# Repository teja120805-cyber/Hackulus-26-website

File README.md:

# ESP32-C3 Nano

:warning: **Temporary warning**: This version of PCB has not been yet validated and it is actively being worked on

Compact and minimalist **ESP32-C3** breakout designed in [KiCAD](https://www.kicad.org/)

## Features
- **Breadboard friendly**
- **Compact dimensions** - 46 x 21.5 mm
- **USB-C** connector for programming (using CDC, so no external usb-serial convertor)
- **External VIN pin** with schottky diode (so both VIN and USB power can be applied at the same time)
- **Low dropout regulator to 3V3** (LDO)
- **Reset** and **Boot** buttons on board
- **Integrated PCB antenna**
- **USB ESD protection**
- Chip: **ESP32-C3FH4**

## Interactive HTML BOM
Thanks to the awesome KiCAD [IBOM](https://github.com/openscopeproject/InteractiveHtmlBom) plugin, we can now generate this stunning BOM! You can find it in docs/ibom.html

## Schematics

## Contributors:
- **SZKANDERA Filip** (filip.szkandera@gmail.com, [@FilipSzkandera](https://github.com/FilipSzkandera/))
- **FRYČÁK Tadeáš** (info@frycak.com, [@TadeasFrycak](https://github.com/TadeasFrycak/))

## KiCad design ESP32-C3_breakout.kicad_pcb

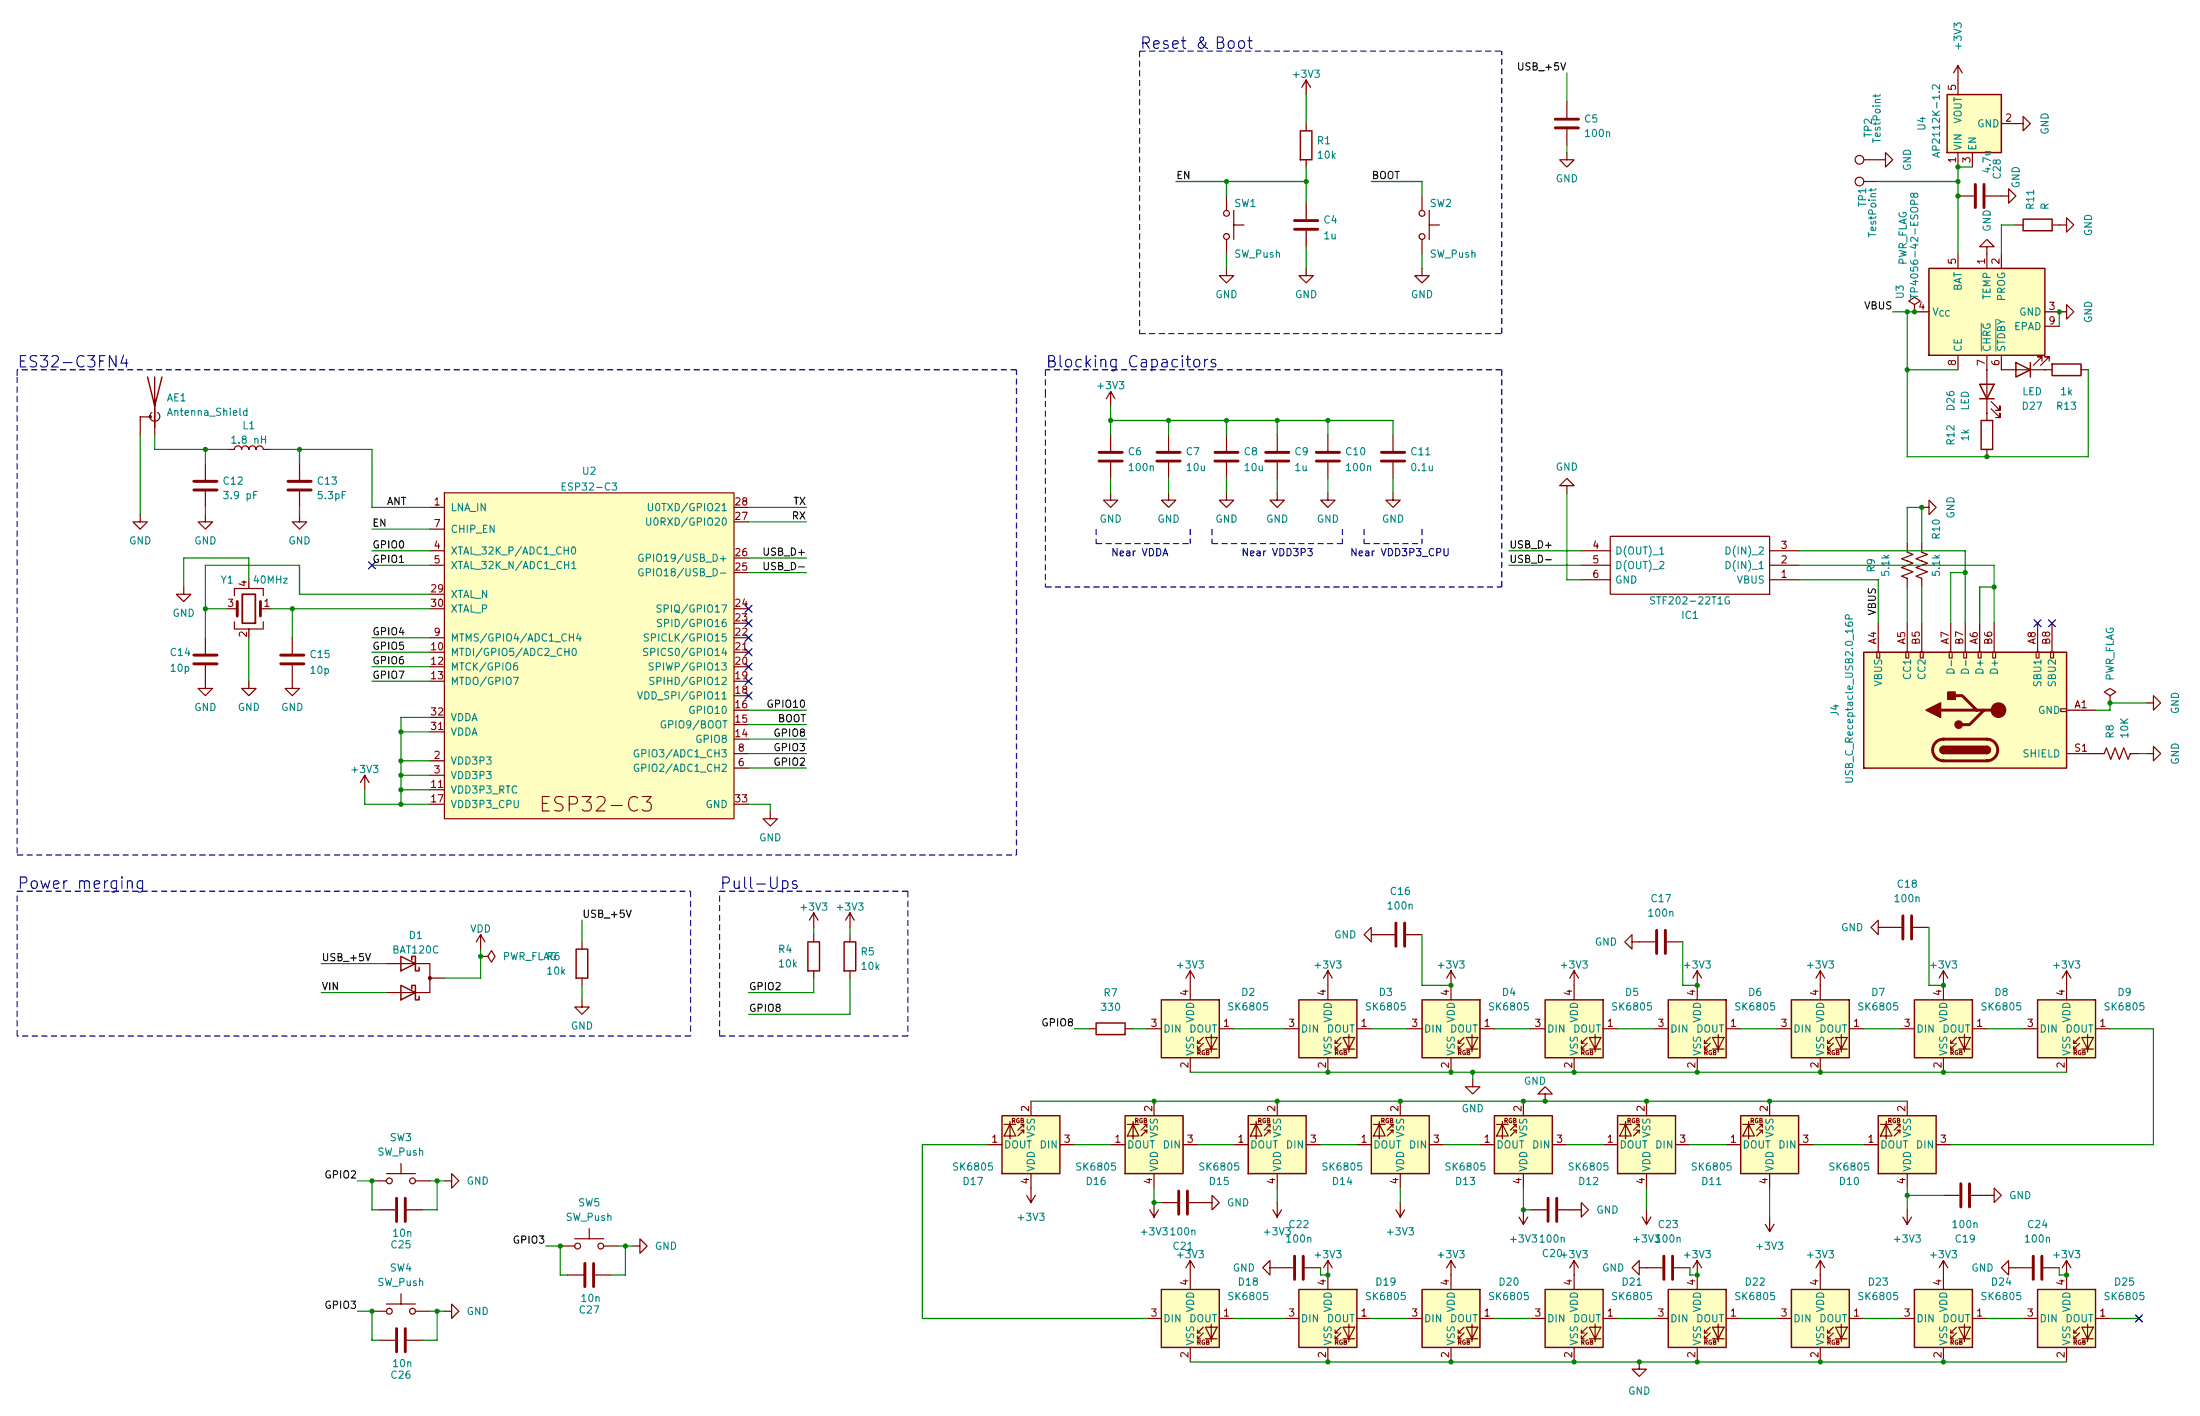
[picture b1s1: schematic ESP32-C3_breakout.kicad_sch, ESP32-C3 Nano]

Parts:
AE1: Antenna_Shield; ESPRESSIF_ESP32_MIFA_2.4GHz_Right
C4, C9: 1u; C_0603_1608Metric
C5, C6, C10, C16, C17, C18, C19, C20, C21, C22, C23, C24: 100n; C_0603_1608Metric
C7, C8: 10u; C_0603_1608Metric
C11: 0.1u; C_0603_1608Metric
C12: 3.9 pF; C_0603_1608Metric
C13: 5.3pF; C_0603_1608Metric
C14, C15: 10p; C_0603_1608Metric
C25, C26, C27: 10n; C_0603_1608Metric
C28: 4.7u; C_0603_1608Metric
D1: BAT120C; SOT-223
D2, D3, D4, D5, D6, D7, D8, D9, D10, D11, D12, D13, D14, D15, D16, D17, D18, D19, D20, D21, D22, D23, D24, D25: SK6805; LED_SK6805_PLCC4_2.4x2.7mm_P1.3mm
D26, D27: LED; LED_0603_1608Metric
IC1: STF202-22T1G; TSOP-6_1.65x3.05mm_P0.95mm; Manufacturer_Part_Number STF202-22T1G; Mouser Part Number 863-STF202-22T1G
J4: USB_C_Receptacle_USB2.0_16P; USB_C_Receptacle_HRO_TYPE-C-31-M-12
L1: 1.8 nH; L_0603_1608Metric
R1, R4, R5, R6: 10k; R_0603_1608Metric
R7: 330; LED_SK6805_PLCC4_2.4x2.7mm_P1.3mm
R8: 10K; R_0603_1608Metric_Pad0.98x0.95mm_HandSolder
R9, R10: 5.1k; R_0603_1608Metric_Pad0.98x0.95mm_HandSolder
R11: R; LED_SK6805_PLCC4_2.4x2.7mm_P1.3mm
R12, R13: 1k; LED_SK6805_PLCC4_2.4x2.7mm_P1.3mm
SW1, SW2: SW_Push; SW_SPST_PTS810
SW3, SW4, SW5: SW_Push; Texas_RVA_VQFN-16-1EP_3.5x3.5mm_P0.5mm_EP2.14x2.14mm_Therma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
TP1, TP2: TestPoint; TestPoint_Pad_1.0x1.0mm
U2: ESP32-C3; QFN-32-1EP_5x5mm_P0.5mm_EP3.45x3.45mm
U3: TP4056-42-ESOP8; SOIC-8-1EP_3.9x4.9mm_P1.27mm_EP2.41x3.3mm_ThermalVias
U4: AP2112K-1.2; SOT-23-5
Y1: 40MHz; Crystal_SMD_2016-4Pin_2.0x1.6mm

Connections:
+3V3: C6.1, C7.1, C8.1, C9.1, C10.1, C11.1, C16.2, C17.2, C18.2, C19.2, C20.2, C21.2, C22.2, C23.2, C24.2, D2.4 (VDD), D3.4 (VDD), D4.4 (VDD), D5.4 (VDD), D6.4 (VDD), D7.4 (VDD), D8.4 (VDD), D9.4 (VDD), D10.4 (VDD), D11.4 (VDD), D12.4 (VDD), D13.4 (VDD), D14.4 (VDD), D15.4 (VDD), D16.4 (VDD), D17.4 (VDD), D18.4 (VDD), D19.4 (VDD), D20.4 (VDD), D21.4 (VDD), D22.4 (VDD), D23.4 (VDD), D24.4 (VDD), D25.4 (VDD), R1.1, R4.1, R5.1, U2.2 (VDD3P3), U2.3 (VDD3P3), U2.11 (VDD3P3_RTC), U2.17 (VDD3P3_CPU), U2.31 (VDDA), U2.32 (VDDA), U4.5 (VOUT)
/ANT: C13.1, L1.1, U2.1 (LNA_IN)
/BOOT: SW2.1, U2.15 (GPIO9/BOOT)
/EN: C4.1, R1.2, SW1.1, U2.7 (CHIP_EN)
/GPIO0: U2.4 (XTAL_32K_P/ADC1_CH0)
/GPIO1: U2.5 (XTAL_32K_N/ADC1_CH1)
/GPIO2: C25.2, R4.2, SW3.1, U2.6 (GPIO2/ADC1_CH2)
/GPIO3: C26.2, C27.2, SW4.1, SW5.1, U2.8 (GPIO3/ADC1_CH3)
/GPIO4: U2.9 (MTMS/GPIO4/ADC1_CH4)
/GPIO5: U2.10 (MTDI/GPIO5/ADC2_CH0)
/GPIO6: U2.12 (MTCK/GPIO6)
/GPIO7: U2.13 (MTDO/GPIO7)
/GPIO8: R5.2, R7.1, U2.14 (GPIO8)
/GPIO10: U2.16 (GPIO10)
/RX: U2.27 (U0RXD/GPIO20)
/TX: U2.28 (U0TXD/GPIO21)
/USB_+5V: C5.1, D1.1 (A1), R6.1
/USB_D+: IC1.4 (D(OUT)_1), U2.26 (GPIO19/USB_D+)
/USB_D-: IC1.5 (D(OUT)_2), U2.25 (GPIO18/USB_D-)
/VBUS: IC1.1 (VBUS), J4.A4 (VBUS), J4.A9 (VBUS), J4.B4 (VBUS), J4.B9 (VBUS), R12.1, R13.1, U3.4 (V_{CC}), U3.8 (CE)
/VIN: D1.3 (A2)
GND: AE1.2 (Shield), C4.2, C5.2, C6.2, C7.2, C8.2, C9.2, C10.2, C11.2, C12.2, C13.2, C14.2, C15.2, C16.1, C17.1, C18.1, C19.1, C20.1, C21.1, C22.1, C23.1, C24.1, C25.1, C26.1, C27.1, C28.2, D2.2 (VSS), D3.2 (VSS), D4.2 (VSS), D5.2 (VSS), D6.2 (VSS), D7.2 (VSS), D8.2 (VSS), D9.2 (VSS), D10.2 (VSS), D11.2 (VSS), D12.2 (VSS), D13.2 (VSS), D14.2 (VSS), D15.2 (VSS), D16.2 (VSS), D17.2 (VSS), D18.2 (VSS), D19.2 (VSS), D20.2 (VSS), D21.2 (VSS), D22.2 (VSS), D23.2 (VSS), D24.2 (VSS), D25.2 (VSS), IC1.6 (GND), J4.A1 (GND), J4.A12 (GND), J4.B1 (GND), J4.B12 (GND), R6.2, R8.2, R9.2, R10.1, R11.2, SW1.2, SW2.2, SW3.2, SW4.2, SW5.2, TP2.1 (1_1), U2.33 (GND), U3.1 (TEMP), U3.3 (GND), U3.9 (EPAD), U4.2 (GND), Y1.2, Y1.4
unnamed: AE1.1 (A), C12.1, L1.2
unnamed: D2.3 (DIN), R7.2
unnamed: D2.1 (DOUT), D3.3 (DIN)
unnamed: D3.1 (DOUT), D4.3 (DIN)
unnamed: D4.1 (DOUT), D5.3 (DIN)
unnamed: D5.1 (DOUT), D6.3 (DIN)
unnamed: D6.1 (DOUT), D7.3 (DIN)
unnamed: D7.1 (DOUT), D8.3 (DIN)
unnamed: D8.1 (DOUT), D9.3 (DIN)
unnamed: D9.1 (DOUT), D10.3 (DIN)
unnamed: D10.1 (DOUT), D11.3 (DIN)
unnamed: D11.1 (DOUT), D12.3 (DIN)
unnamed: D12.1 (DOUT), D13.3 (DIN)
unnamed: D13.1 (DOUT), D14.3 (DIN)
unnamed: D14.1 (DOUT), D15.3 (DIN)
unnamed: D15.1 (DOUT), D16.3 (DIN)
unnamed: D16.1 (DOUT), D17.3 (DIN)
unnamed: D17.1 (DOUT), D18.3 (DIN)
unnamed: D18.1 (DOUT), D19.3 (DIN)
unnamed: D19.1 (DOUT), D20.3 (DIN)
unnamed: D20.1 (DOUT), D21.3 (DIN)
unnamed: D21.1 (DOUT), D22.3 (DIN)
unnamed: D22.1 (DOUT), D23.3 (DIN)
unnamed: D23.1 (DOUT), D24.3 (DIN)
unnamed: D24.1 (DOUT), D25.3 (DIN)
unnamed: D26.2 (A), U3.7 (~CHRG)
unnamed: D26.1 (K), R12.2
unnamed: D27.2 (A), U3.6 (~STDBY)
unnamed: D27.1 (K), R13.2
unnamed: IC1.2 (D(IN)_1), J4.A6 (D+), J4.B6 (D+)
unnamed: IC1.3 (D(IN)_2), J4.A7 (D-), J4.B7 (D-)
unnamed: J4.A5 (CC1), R9.1
unnamed: J4.B5 (CC2), R10.2
unnamed: J4.S1 (SHIELD), R8.1
unnamed: C14.1, U2.29 (XTAL_N), Y1.3
unnamed: C15.1, U2.30 (XTAL_P), Y1.1
unnamed: C28.1, TP1.1 (1_1), U3.5 (BAT), U4.1 (VIN), U4.3 (EN)
unnamed: R11.1, U3.2 (PROG)
VDD: D1.4 (K)

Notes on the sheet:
Near VDD3P3_CPU
Reset & Boot
ES32-C3FN4
Power merging
Near VDDA
Near VDD3P3
Pull-Ups
Blocking Capacitors

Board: 2 copper layers, 77 parts (0 on the bottom side), 49 nets, no tracks yet.
